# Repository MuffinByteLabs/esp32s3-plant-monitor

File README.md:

# ESP32-S3 Plant Monitor — Rev A

**Ray Malik** · [muffinbytelabs.com](https://muffinbytelabs.com) · [muffinbytelabs@gmail.com](mailto:muffinbytelabs@gmail.com)

A solo hardware project taken the whole way: requirements → schematic capture → 4-layer layout → DFM → fab and assembly order → bring-up. Every schematic, review, waiver and decision in this repo is my own work.

Wi-Fi plant monitor: soil moisture, temperature / humidity / pressure, and ambient light, USB-C powered with 1-cell LiPo charging and automatic USB↔battery hand-over. Native-USB programming, no bridge chip. KiCad 10 hierarchical schematic, **4-layer board** (signal / GND / GND / signal, JLC04161H-7628), 62.5 × 44.5 mm, ordered fabricated and assembled at JLCPCB on **2026-08-21**.

| | |
|---|---|
| **MCU** | ESP32-S3-WROOM-1-N8, native USB — no bridge chip |
| **Sensors** | BME280 (temperature / humidity / pressure) · VEML7700 (ambient light) · DFRobot SEN0193 capacitive soil probe |
| **Power** | USB-C 5 V → PPTC + TVS → AP2112K-3.3 (600 mA) · MCP73831 1S LiPo charger · discrete USB↔battery load share, hand-over in ≈50–100 ms |
| **Sleep** | ≈210 µA as built (≈90 µA with the power LED unfitted) ⇒ ~100 days on a 500 mAh cell |
| **Board** | 62.5 × 44.5 mm · 4-layer, JLC04161H-7628 · 1.6 mm · lead-free HASL · 404 track segments, 154 vias |
| **Verification** | 6 written reviews · 20 packages / 69 placements checked against datasheets |
| **Built** | 5 boards fabricated + assembled for ≈$49 after coupons, every part pre-stocked in the JLC library |
| **Tools** | KiCad 10 · JLCPCB Standard PCBA |

## Start here

Everything below opens in the browser — no KiCad install, no downloads.

| | |
|---|---|
| 📐 **[Schematic (PDF, 8 sheets)](docs/ESP32S3_PlantMonitor_RevA_Schematic.pdf)** | The whole design, plotted from the board file that was ordered |
| 📄 **[Design document](docs/ESP32S3_Plant_Monitor_Final_Design_Document.md)** | Every component and why it is there, written to be read by someone who is not a PCB engineer |
| 🔍 **[Design reviews — 6 on file](docs/reviews/)** | Real review records with findings, severities and fixes. The pre-fab review caught **3 blocking errors** — floating USB-C ground pins, a missing battery-sense chain, and a stale BOM — all resolved before ordering |
| 🧭 **[What I'd change in Rev B](docs/RevB_Upgrade_Plan.md)** | Ranked upgrades with a three-way charger-IC comparison and a costed path from 210 µA to 15–35 µA |
| 🧪 **[Engineering notes](docs/Engineering_Notes.md)** | Bench measurements: soil calibration, the three-layer battery-protection analysis, the hand-over walkthrough |
| 🏭 **[Frozen manufacturing package](fabrication/revA/)** | The exact gerber zip, BOM and CPL uploaded to JLCPCB, beside [`ORDER_NOTES.md`](fabrication/revA/ORDER_NOTES.md) — every setting the board was ordered with |
| 🔧 **[Bring-up guide](docs/BringUp_Guide.md)** | First-power procedure, expected voltages, probe points, troubleshooting |
| 🖨 **[Fab layer plots (PDF)](docs/ESP32S3_PlantMonitor_RevA_FabLayers.pdf)** | All four copper layers, both silks, mask and paste — what the fab actually receives |

| Top | Bottom |
|---|---|
|  |  |

## What this board demonstrates

- **4-layer discipline** — dual unbroken ground planes, zero signals on the inner layers, a via at every decoupler, stitching around the antenna keep-out.
- **RF module integration** — antenna nose overhanging the board edge, all-layer keepout, ground ring, and a panel-rail instruction written into the fab remark so breakaway tabs cannot sit under the overhang.
- **USB 2.0 pair** at ≈90 Ω coupled geometry, length-matched, no vias, ESD in copper order.
- **Power-path design with numbers** — fuse → TVS → LDO, an automatic USB↔battery hand-over sized so the switch completes in ≈50–100 ms, and a 210 µA sleep budget with a named dominant contributor.
- **Manufacturing fluency** — DFM checked against JLCPCB's live capability pages, part-tier economics understood before ordering, pre-stocked parts library, DDP tariff handling.
- **A documentation trail** — two design reviews, a placement review, a finishing review, a final layout audit, and order notes, all on record here.

## What I'd change in Rev B

- **The power path is discrete, and it shows.** MCP73831 + Schottky + P-FET load-sharing works, but it has a ≈50–100 ms body-diode notch at USB unplug, a Vgs-dependent switch point, and no charge safety timer. Rev B replaces the four-part cluster with one IC — [BQ24075 vs MCP73871 vs TPS2113A, compared](docs/RevB_Upgrade_Plan.md#1-integrated-power-path-the-headline-upgrade).
- **210 µA of sleep current is too high**, and the power LED alone is 120 µA of it. LED on a solder jumper, a nanopower LDO, and a switched sense divider get it to 15–35 µA — months to years of standby instead of weeks.
- **No series element on the soil-probe ADC input.** The probe cable is a metre-long antenna into a bare pin; Rev A has only a parallel pull-down. Series resistor plus TVS at J2 next time.
- **Four layers were bought for margin, not for speed.** The fastest signal on this board is USB Full Speed — a disciplined 2-layer board would have worked. The reasoning for spending the extra layers is written down in [`docs/KiCad_Settings_RevA.md`](docs/KiCad_Settings_RevA.md).

<details>
<summary><strong>Repository map</strong> — 24 documents, KiCad sources, frozen fab package, datasheets</summary>

| Path | What |
|---|---|
| [`hardware/`](hardware/) | KiCad 10 project — root sheet + sheets 02–08, libraries in `hardware/libs/`. Library paths are `${KIPRJMOD}`-relative; keep `libs/` inside `hardware/`. |
| [`fabrication/revA/`](fabrication/revA/) | The frozen order package: gerber zip, BOM, CPL, and `ORDER_NOTES.md` (§7 = the as-ordered record) |
| **Documents** | |
| [`docs/ESP32S3_PlantMonitor_RevA_Schematic.pdf`](docs/ESP32S3_PlantMonitor_RevA_Schematic.pdf) | All 8 schematic sheets, plotted from the ordered board file |
| [`docs/ESP32S3_PlantMonitor_RevA_FabLayers.pdf`](docs/ESP32S3_PlantMonitor_RevA_FabLayers.pdf) | Layer-by-layer fab plots |
| [`docs/ESP32S3_Plant_Monitor_Final_Design_Document.md`](docs/ESP32S3_Plant_Monitor_Final_Design_Document.md) | The full design document — as-built designators throughout; Addendum A holds the renumbering record |
| [`docs/PROJECT_STATUS.md`](docs/PROJECT_STATUS.md) | Rev A order and build log: what was ordered, what it cost, order-day problems and fixes, waivers on record |
| [`docs/BringUp_Guide.md`](docs/BringUp_Guide.md) | First-power procedure, expected voltages, probe points |
| [`docs/PinMap_CheatSheet.md`](docs/PinMap_CheatSheet.md) | GPIO / net / connector map, as built |
| [`docs/Engineering_Notes.md`](docs/Engineering_Notes.md) | Bench notes: calibration values, battery-protection analysis, hand-over walkthrough |
| [`docs/ESP32S3_PlantMonitor_RevA_BOM.md`](docs/ESP32S3_PlantMonitor_RevA_BOM.md) | BOM as a readable table (the [`.xlsx`](docs/ESP32S3_PlantMonitor_RevA_BOM.xlsx) is the editable source) |
| **Layout rulebooks** | |
| [`docs/Hard_Rules_Layout_RevA.md`](docs/Hard_Rules_Layout_RevA.md) | The graded rulebook — LAW vs STRONG PRACTICE, plus 4-layer amendments |
| [`docs/Routing_Guide_RevA_4Layer.md`](docs/Routing_Guide_RevA_4Layer.md) | Layer strategy, net-by-net routing order, via craft |
| [`docs/KiCad_Settings_RevA.md`](docs/KiCad_Settings_RevA.md) | Every board-setup value and the reasoning behind it |
| [`docs/Layout_Readiness_and_Placement_Guide_RevA.md`](docs/Layout_Readiness_and_Placement_Guide_RevA.md) | Footprint verification + placement playbook |
| [`docs/Footprint_Check_ESP32S3_PlantMonitor_RevA.md`](docs/Footprint_Check_ESP32S3_PlantMonitor_RevA.md) | All 20 packages / 69 placements, each checked against its datasheet |
| [`docs/Footprint_Terms_and_Leeway_Guide.md`](docs/Footprint_Terms_and_Leeway_Guide.md) | Plain-English footprint terms and how much tolerance actually matters |
| [`docs/Fabrication_File_Primer.md`](docs/Fabrication_File_Primer.md) | What each gerber and drill file is, and why |
| [`docs/Finishing_Guide_RevA.md`](docs/Finishing_Guide_RevA.md) | Silkscreen, branding and pre-order finishing pass |
| [`docs/RevB_Upgrade_Plan.md`](docs/RevB_Upgrade_Plan.md) | Ranked upgrades, integrated power path first |
| **Reviews** | |
| [`docs/reviews/`](docs/reviews/README.md) | All six reviews, [indexed here](docs/reviews/README.md) with date, scope, method and outcome |
| **References** | |
| [`references/datasheets/`](references/datasheets/) | Vendor datasheets for every part — [indexed here](references/datasheets/README.md) |
| [`references/JLCPCB_Capabilities_2026-08.md`](references/JLCPCB_Capabilities_2026-08.md) | Capability quick-sheet used for DFM |
| [`references/reference-designs/`](references/reference-designs/) | Espressif DevKitC-1 schematic |
| [`firmware/`](firmware/) | The hardware→firmware contract: thresholds, sequences and pin duties the board imposes |

</details>

## What's next

Boards arrive early September. Bring-up follows [`docs/BringUp_Guide.md`](docs/BringUp_Guide.md) — measured results go into its record sheet, and a photograph of the working board replaces the render above.

Questions, or hiring: **[muffinbytelabs@gmail.com](mailto:muffinbytelabs@gmail.com)** · [muffinbytelabs.com](https://muffinbytelabs.com)

## License

Hardware design files and documentation are released under the **CERN Open Hardware Licence v2 — Permissive** (see [`LICENSE`](LICENSE)). Vendor datasheets in `references/datasheets/` remain the property of their respective manufacturers and are included for convenience only.

## Safety notes for anyone building this board

1. **Meter the battery plug polarity** before it ever touches J3 — the charge LED is not proof of polarity.
2. **Protected cells only**, and never store the board with a battery attached (≈210 µA sleep floor).
3. **Firmware enforces the battery limits**: no Wi-Fi TX below ~3.5 V, deep sleep at 3.0 V.

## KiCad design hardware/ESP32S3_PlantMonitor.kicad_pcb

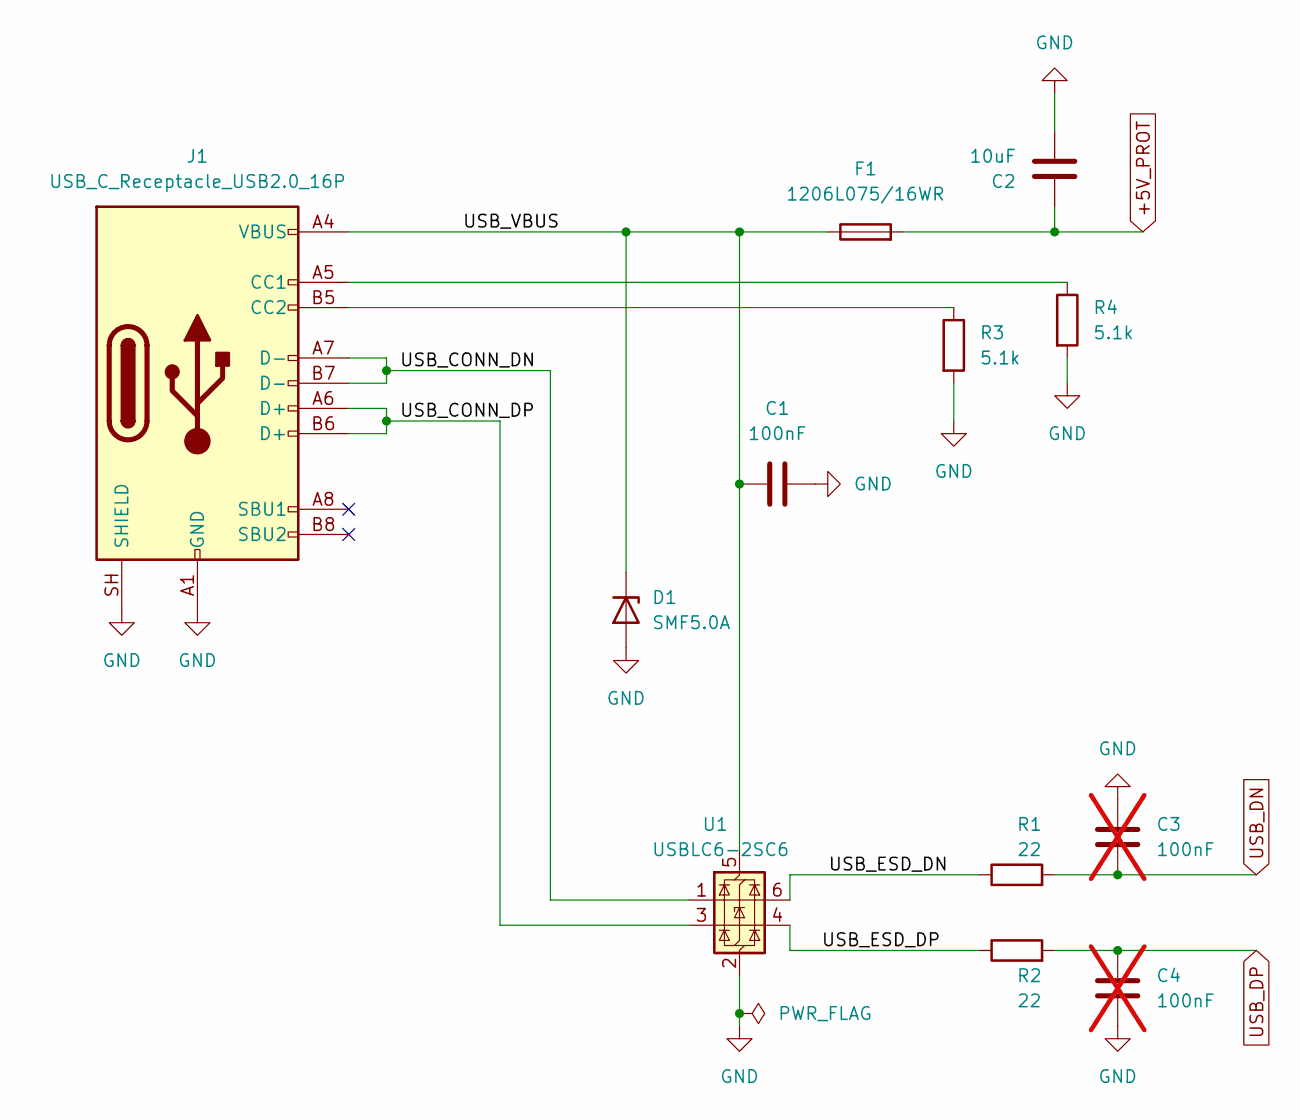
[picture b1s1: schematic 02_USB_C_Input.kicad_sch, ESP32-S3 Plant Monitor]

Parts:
C1: 100nF; C_0603_1608Metric; LCSC Part C14663
C2: 10uF; C_0805_2012Metric; LCSC Part C15850
C3, C4: 100nF; C_0603_1608Metric; LCSC Part C14663; not fitted
D1: SMF5.0A; D_SOD-123F; LCSC Part C2980403
F1: 1206L075/16WR; Fuse_1206_3216Metric; LCSC Part C371166
J1: USB_C_Receptacle_USB2.0_16P; USB_C_Receptacle_HRO_TYPE-C-31-M-12; LCSC Part C165948
R1, R2: 22; R_0603_1608Metric; LCSC Part C23345
R3, R4: 5.1k; R_0603_1608Metric; LCSC Part C23186
U1: USBLC6-2SC6; SOT-23-6; LCSC Part C7519

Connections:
+5V_PROT: C2.1, F1.2; also elsewhere on the board
/02_USB_C_Input/USB_CONN_DN: J1.A7 (D-), J1.B7 (D-), U1.1 (I/O1)
/02_USB_C_Input/USB_CONN_DP: J1.A6 (D+), J1.B6 (D+), U1.3 (I/O2)
/02_USB_C_Input/USB_ESD_DN: R1.1, U1.6 (I/O1)
/02_USB_C_Input/USB_ESD_DP: R2.1, U1.4 (I/O2)
/02_USB_C_Input/USB_VBUS: C1.1, D1.1 (K), F1.1, J1.A4 (VBUS), J1.A9 (VBUS), J1.B4 (VBUS), J1.B9 (VBUS), U1.5 (VBUS)
GND: C1.2, C2.2, C3.2, C4.1, D1.2 (A), J1.A1 (GND), J1.A12 (GND), J1.B1 (GND), J1.B12 (GND), J1.SH (SHIELD), R3.2, R4.2, U1.2 (GND); also elsewhere on the board
unnamed: J1.A5 (CC1), R4.1
unnamed: J1.B5 (CC2), R3.1
USB_DN: C3.1, R1.2; also elsewhere on the board
USB_DP: C4.2, R2.2; also elsewhere on the board

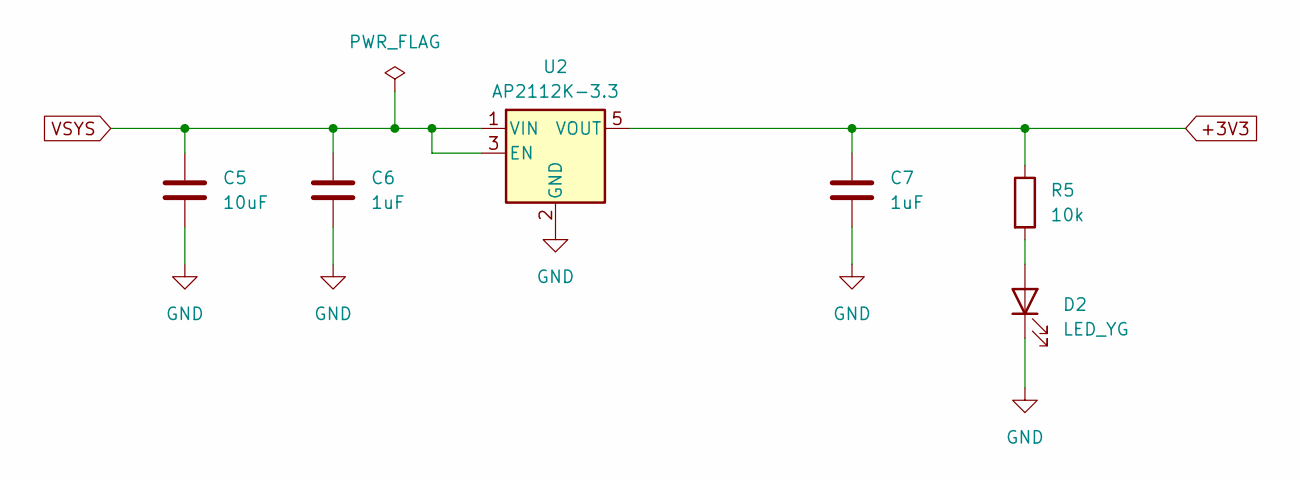
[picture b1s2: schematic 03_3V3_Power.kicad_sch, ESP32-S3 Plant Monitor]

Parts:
C5: 10uF; C_0805_2012Metric; LCSC Part C15850
C6, C7: 1uF; C_0603_1608Metric; LCSC Part C15849
D2: LED_YG; LED_0603_1608Metric; LCSC Part C2289
R5: 10k; R_0603_1608Metric; LCSC Part C25804
U2: AP2112K-3.3; SOT-23-5; LCSC Part C51118

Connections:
+3V3: C7.1, R5.1, U2.5 (VOUT); also elsewhere on the board
GND: C5.2, C6.2, C7.2, D2.1 (K), U2.2 (GND); also elsewhere on the board
unnamed: D2.2 (A), R5.2
VSYS: C5.1, C6.1, U2.1 (VIN), U2.3 (EN); also elsewhere on the board

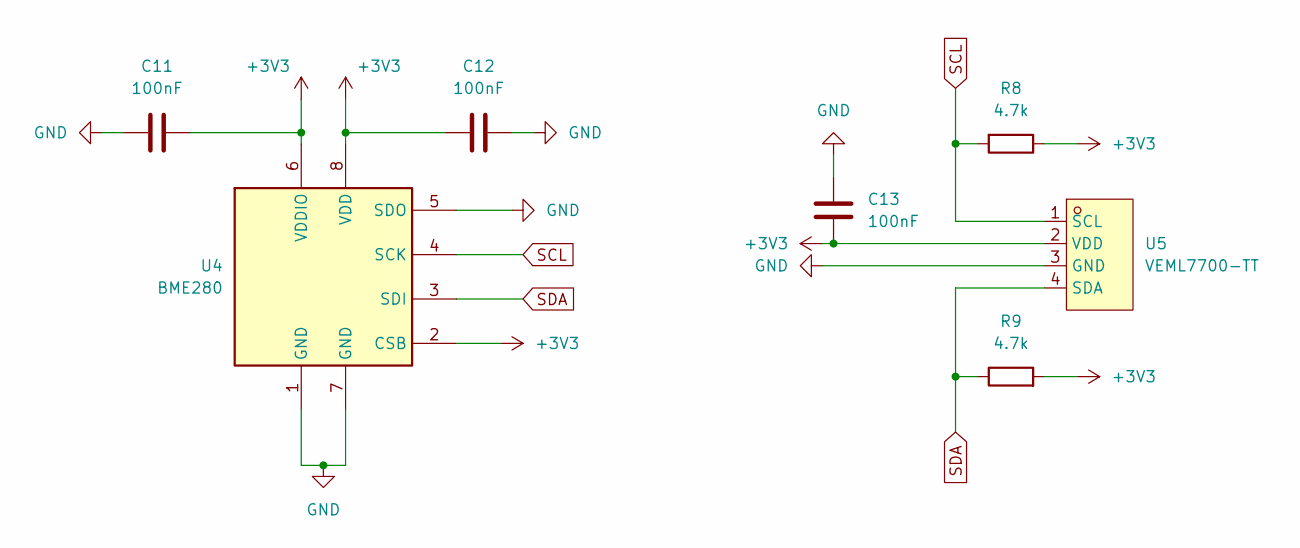
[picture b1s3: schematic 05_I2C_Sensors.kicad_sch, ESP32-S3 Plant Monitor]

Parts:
C11, C12, C13: 100nF; C_0603_1608Metric; LCSC Part C14663
R8, R9: 4.7k; R_0603_1608Metric; LCSC Part C23162
U4: BME280; Bosch_LGA-8_2.5x2.5mm_P0.65mm_ClockwisePinNumbering; LCSC Part C92489
U5: VEML7700-TT; SENSOR-SMD_EML7700-TT; MPN VEML7700-TT; LCSC Part C1850416

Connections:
+3V3: C11.2, C12.2, C13.2, R8.1, R9.2, U4.2 (CSB), U4.6 (VDDIO), U4.8 (VDD), U5.2 (VDD); also elsewhere on the board
GND: C11.1, C12.1, C13.1, U4.1 (GND), U4.5 (SDO), U4.7 (GND), U5.3 (GND); also elsewhere on the board
SCL: R8.2, U4.4 (SCK), U5.1 (SCL); also elsewhere on the board
SDA: R9.1, U4.3 (SDI), U5.4 (SDA); also elsewhere on the board

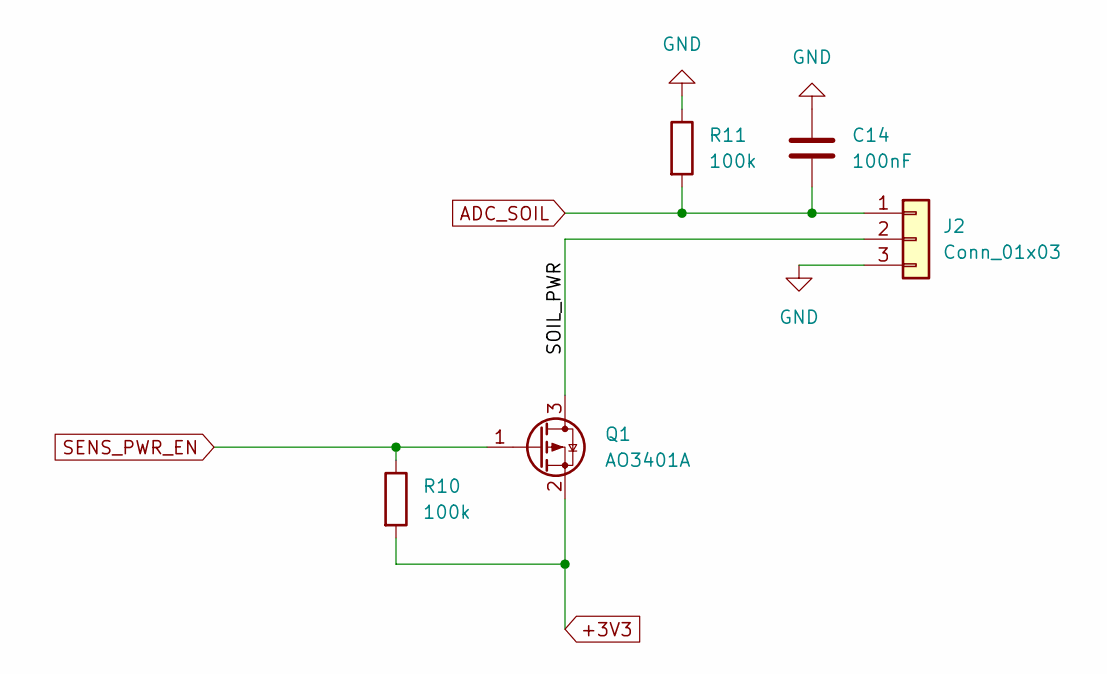
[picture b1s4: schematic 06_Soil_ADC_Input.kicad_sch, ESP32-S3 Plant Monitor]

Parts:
C14: 100nF; C_0603_1608Metric; LCSC Part C14663
J2: Conn_01x03; JST_PH_S3B-PH-K_1x03_P2.00mm_Horizontal; LCSC Part C157929
Q1: AO3401A; SOT-23; LCSC Part C15127
R10, R11: 100k; R_0603_1608Metric; LCSC Part C25803

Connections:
+3V3: Q1.2 (S), R10.2; also elsewhere on the board
/06_Soil_Probe_Input/SOIL_PWR: J2.2, Q1.3 (D)
ADC_SOIL: C14.2, J2.1, R11.2; also elsewhere on the board
GND: C14.1, J2.3, R11.1; also elsewhere on the board
SENS_PWR_EN: Q1.1 (G), R10.1; also elsewhere on the board

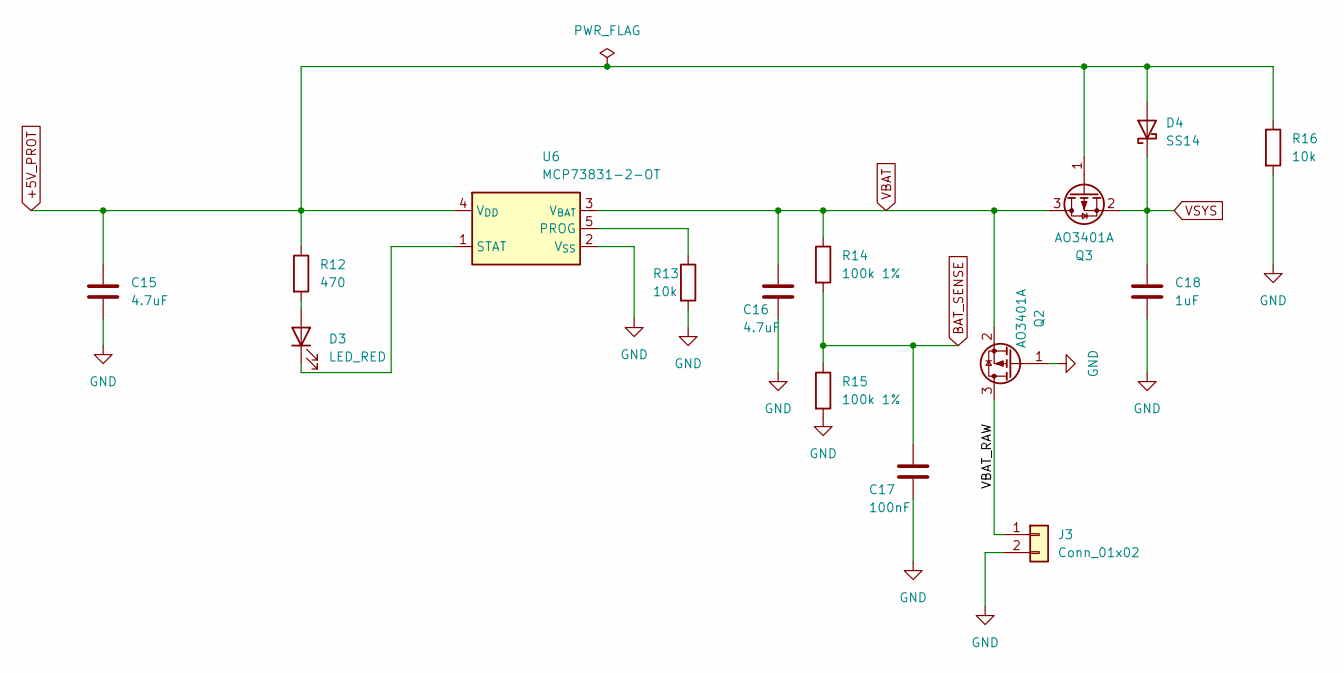
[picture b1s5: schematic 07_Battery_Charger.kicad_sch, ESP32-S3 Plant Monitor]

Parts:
C15, C16: 4.7uF; C_0603_1608Metric; LCSC Part C19666
C17: 100nF; C_0603_1608Metric; LCSC Part C14663
C18: 1uF; C_0603_1608Metric; LCSC Part C15849
D3: LED_RED; LED_0603_1608Metric; LCSC Part C2286
D4: SS14; D_SMA; LCSC Part C2480
J3: Conn_01x02; JST_PH_S2B-PH-K_1x02_P2.00mm_Horizontal; LCSC Part C173752
Q2, Q3: AO3401A; SOT-23; LCSC Part C15127
R12: 470; R_0603_1608Metric; LCSC Part C23179
R13, R16: 10k; R_0603_1608Metric; LCSC Part C25804
R14, R15: 100k 1%; R_0603_1608Metric; LCSC Part C25803
U6: MCP73831-2-OT; SOT-23-5; LCSC Part C424093

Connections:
+5V_PROT: C15.1, D4.2 (A), Q3.1 (G), R12.1, R16.1, U6.4 (V_{DD}); also elsewhere on the board
/07_Battery_PowerPath/VBAT_RAW: J3.1, Q2.3 (D)
BAT_SENSE: C17.1, R14.2, R15.1; also elsewhere on the board
GND: C15.2, C16.2, C17.2, C18.2, J3.2, Q2.1 (G), R13.2, R15.2, R16.2, U6.2 (V_{SS}); also elsewhere on the board
unnamed: D3.2 (A), R12.2
unnamed: D3.1 (K), U6.1 (STAT)
unnamed: R13.1, U6.5 (PROG)
VBAT: C16.1, Q2.2 (S), Q3.3 (D), R14.1, U6.3 (V_{BAT}); also elsewhere on the board
VSYS: C18.1, D4.1 (K), Q3.2 (S); also elsewhere on the board

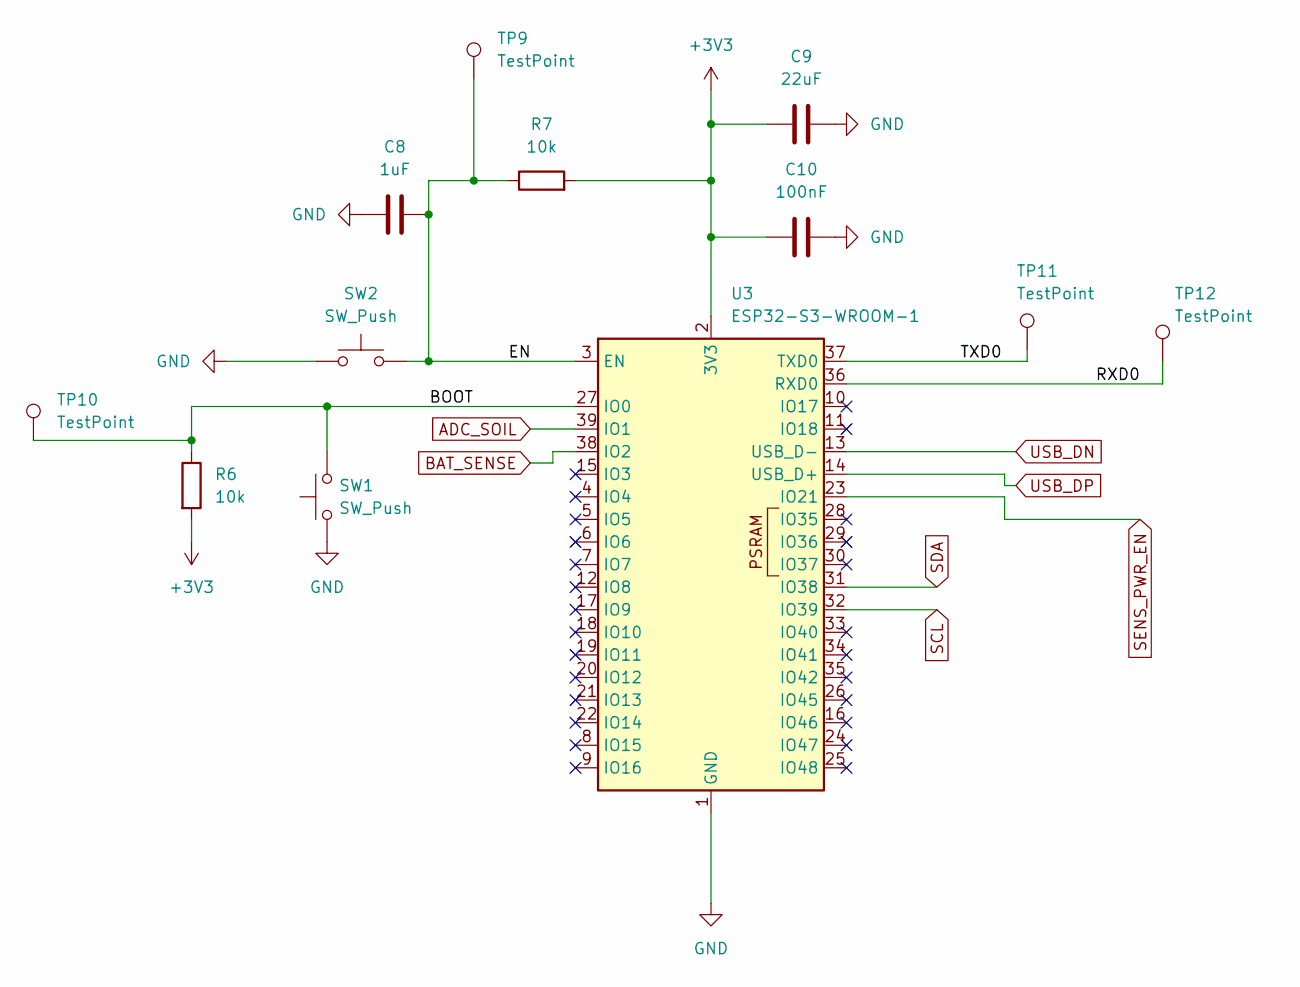
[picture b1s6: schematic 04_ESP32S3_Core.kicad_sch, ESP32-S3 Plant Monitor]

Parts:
C8: 1uF; C_0603_1608Metric; LCSC Part C15849
C9: 22uF; C_0805_2012Metric; LCSC Part C45783
C10: 100nF; C_0603_1608Metric; LCSC Part C14663
R6, R7: 10k; R_0603_1608Metric; LCSC Part C25804
SW1, SW2: SW_Push; SW-SMD_4P-L5.1-W5.1-P3.70-LS6.5-TL_H1.5; LCSC Part C318884
TP9, TP10: TestPoint; TestPoint_Pad_D1.5mm
TP11, TP12: TestPoint; TestPoint_THTPad_D2.0mm_Drill1.0mm
U3: ESP32-S3-WROOM-1; LCSC Part C2913198

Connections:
+3V3: C9.1, C10.1, R6.2, R7.2, U3.2 (3V3); also elsewhere on the board
/04_ESP32S3_Core/BOOT: R6.1, SW1.2, TP10.1 (1_1), U3.27 (IO0)
/04_ESP32S3_Core/EN: C8.2, R7.1, SW2.2, TP9.1 (1_1), U3.3 (EN)
/04_ESP32S3_Core/RXD0: TP12.1 (1_1), U3.36 (RXD0)
/04_ESP32S3_Core/TXD0: TP11.1 (1_1), U3.37 (TXD0)
ADC_SOIL: U3.39 (IO1); also elsewhere on the board
BAT_SENSE: U3.38 (IO2); also elsewhere on the board
GND: C8.1, C9.2, C10.2, SW1.1, SW2.1, U3.1 (GND), U3.40 (GND), U3.41 (GND); also elsewhere on the board
SCL: U3.32 (IO39); also elsewhere on the board
SDA: U3.31 (IO38); also elsewhere on the board
SENS_PWR_EN: U3.23 (IO21); also elsewhere on the board
USB_DN: U3.13 (USB_D-); also elsewhere on the board
USB_DP: U3.14 (USB_D+); also elsewhere on the board

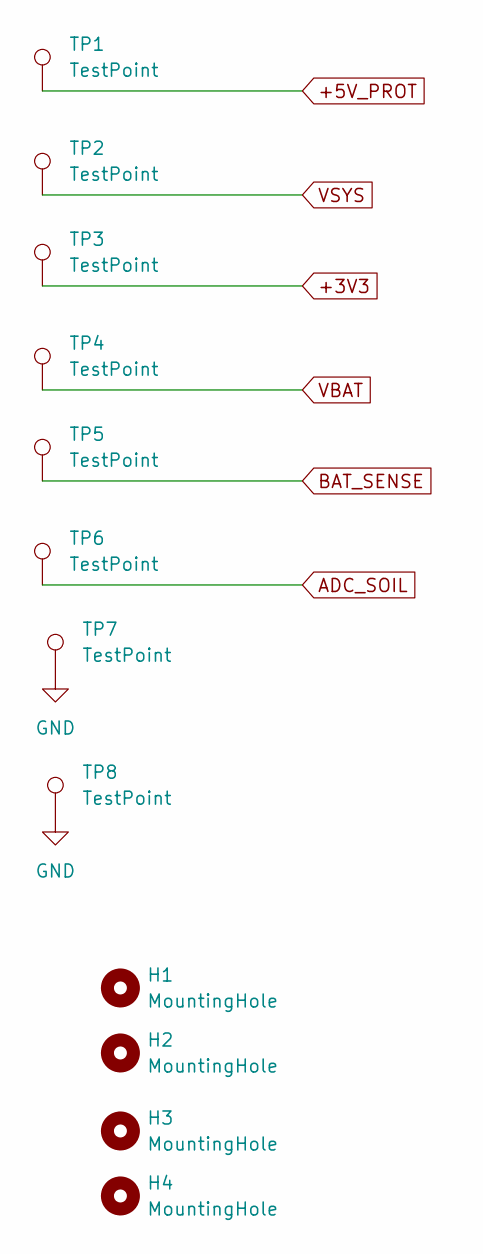
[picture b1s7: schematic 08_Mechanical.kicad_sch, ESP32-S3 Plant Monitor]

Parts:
H1, H2, H3, H4: MountingHole; MountingHole_3.2mm_M3
TP1, TP2, TP3, TP4, TP5, TP6, TP7: TestPoint; TestPoint_Pad_D1.5mm
TP8: TestPoint; TestPoint_THTPad_D2.0mm_Drill1.0mm

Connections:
+3V3: TP3.1 (1_1); also elsewhere on the board
+5V_PROT: TP1.1 (1_1); also elsewhere on the board
ADC_SOIL: TP6.1 (1_1); also elsewhere on the board
BAT_SENSE: TP5.1 (1_1); also elsewhere on the board
GND: TP7.1 (1_1), TP8.1 (1_1); also elsewhere on the board
VBAT: TP4.1 (1_1); also elsewhere on the board
VSYS: TP2.1 (1_1); also elsewhere on the board

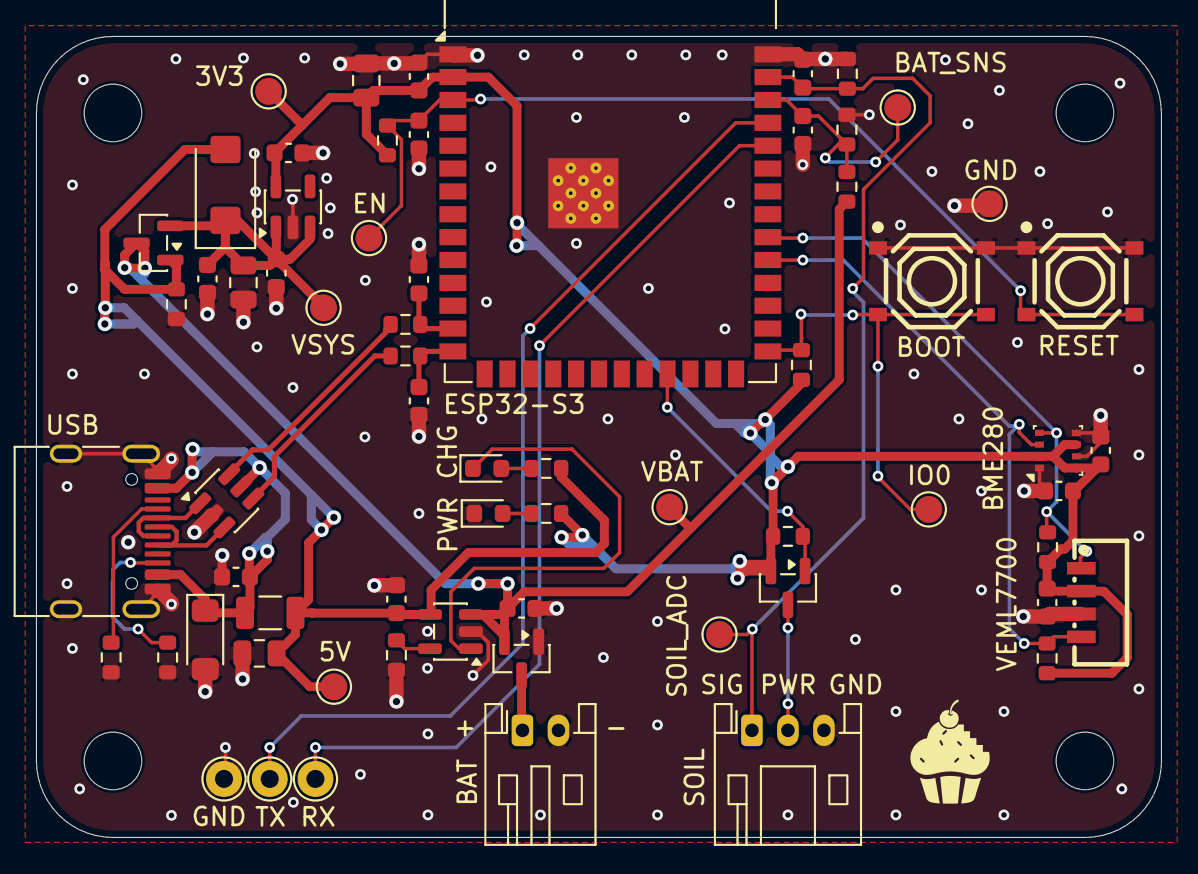
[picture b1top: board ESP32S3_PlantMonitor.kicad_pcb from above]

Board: 4 copper layers, 62.5 x 44.5 mm, 70 parts (0 on the bottom side), 29 nets.

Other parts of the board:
G1: muffinByteLogo_2x

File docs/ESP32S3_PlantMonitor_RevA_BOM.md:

# ESP32-S3 Plant Monitor — Rev A Bill of Materials

*GENERATED FROM THE SCHEMATIC 2026-07-20 (53 parts / 29 lines; LCSC fields verified in-file). The schematic is the master — regenerate this sheet after any change. Library status (Basic/Extended) and stock are LIVE values: re-verify every line on jlcpcb.com/parts at order time. Test points & mounting holes intentionally excluded (bare copper / holes).*

> The spreadsheet this table is generated from lives beside it as [`ESP32S3_PlantMonitor_RevA_BOM.xlsx`](ESP32S3_PlantMonitor_RevA_BOM.xlsx). For what was **actually ordered** on 2026-08-21 — including the two substitutions made on order day — see [`fabrication/revA/BOM-ESP32S3_PlantMonitor.csv`](../fabrication/revA/BOM-ESP32S3_PlantMonitor.csv).

| # | Category | Designators | Qty | Value | MPN | LCSC # | Footprint (package) | Library | Populate | Notes |
|---|---|---|---|---|---|---|---|---|---|---|
| 1 | 1 ICs & module | U1 | 1 | USBLC6-2SC6 | USBLC6-2SC6 | C7519 | SOT-23-6 | Extended | Yes |  |
| 2 | 1 ICs & module | U2 | 1 | AP2112K-3.3 | AP2112K-3.3TRG1 | C51118 | SOT-23-5 | Extended | Yes | 3.3 V / 600 mA |
| 3 | 1 ICs & module | U3 | 1 | ESP32-S3-WROOM-1 | ESP32-S3-WROOM-1-N8 | C2913198 | ESP32-S3-WROOM-1 | Extended | Yes | Standard PCBA tier only (module size) |
| 4 | 1 ICs & module | U4 | 1 | BME280 | BME280 | C92489 | Bosch_LGA-8_2.5x2.5mm_P0.65mm_ClockwisePinNumbering | Extended | Yes | 0x76; keep vent clear, away from heat |
| 5 | 1 ICs & module | U5 | 1 | VEML7700-TT | VEML7700-TT | C1850416 | SENSOR-SMD_EML7700-TT | Extended | Yes | -TT = top-view window; 0x10 |
| 6 | 1 ICs & module | U6 | 1 | MCP73831-2-OT | MCP73831T-2ACI/OT | C424093 | SOT-23-5 | Extended | Yes | 4.20 V variant; PROG 10k -> ~100 mA |
| 7 | 2 Transistors | Q1, Q2, Q3 | 3 | AO3401A | AO3401A | C15127 | SOT-23 | Basic | Yes | Q1 soil switch / Q2 reverse guard / Q3 source select |
| 8 | 3 Diodes & LEDs | D1 | 1 | SMF5.0A | SMF5.0A | C2980403 | D_SOD-123F | Extended | Yes | TVS on USB_VBUS |
| 9 | 3 Diodes & LEDs | D2 | 1 | LED_YG | KT-0603YG | C2289 | LED_0603_1608Metric | Extended | Yes | Yellow-green Vf 2.0-2.2 V (correct chemistry for 3.3 V rail). 30-42 mcd -> dim at 120 uA by design; bench-check. Went Extended 2026-07. |
| 10 | 3 Diodes & LEDs | D3 | 1 | LED_RED | KT-0603R | C2286 | LED_0603_1608Metric | Basic | Yes | Red, ~6 mA from STAT |
| 11 | 3 Diodes & LEDs | D4 | 1 | SS14 | SS14 | C2480 | D_SMA | Basic | Yes | Power-path Schottky |
| 12 | 4 Connectors & electromech | F1 | 1 | 1206L075/16WR | 1206L075/16WR | C371166 | Fuse_1206_3216Metric | Verify | Yes | 0.75 A hold / 1.5 A trip / 16 V |
| 13 | 4 Connectors & electromech | J1 | 1 | USB_C_Receptacle_USB2.0_16P | TYPE-C-31-M-12 | C165948 | USB_C_Receptacle_HRO_TYPE-C-31-M-12 | Extended | Yes | KiCad ships exact footprint. Small handling fee. |
| 14 | 4 Connectors & electromech | J2 | 1 | Conn_01x03 | S3B-PH-K-S(LF)(SN) | C157929 | JST_PH_S3B-PH-K_1x03_P2.00mm_Horizontal | Verify | Yes | Soil: pin1 sig / pin2 pwr / pin3 GND. Buzz out cable. |
| 15 | 4 Connectors & electromech | J3 | 1 | Conn_01x02 | S2B-PH-K-S(LF)(SN) | C173752 | JST_PH_S2B-PH-K_1x02_P2.00mm_Horizontal | Verify | Yes | Battery: pin1 = +. METER PLUG POLARITY FIRST. |
| 16 | 4 Connectors & electromech | SW1, SW2 | 2 | SW_Push | TS-1187A-B-A-B | C318884 | SW-SMD_4P-L5.1-W5.1-P3.70-LS6.5-TL_H1.5 | Basic | Yes | Project footprint, pads renumbered 1/1/2/2 (verified vs datasheet A-B/C-D pairing) |
| 17 | 5 Resistors 0603 | R1, R2 | 2 | 22 | 0603WAF220JT5E | C23345 | R_0603_1608Metric | Basic | Yes | USB series |
| 18 | 5 Resistors 0603 | R10, R11 | 2 | 100k | 0603WAF1003T5E | C25803 | R_0603_1608Metric | Basic | Yes | All +-1% |
| 19 | 5 Resistors 0603 | R12 | 1 | 470 | 0603WAF4700T5E | C23179 | R_0603_1608Metric | Basic | Yes | Charge-LED limit ~6 mA |
| 20 | 5 Resistors 0603 | R13, R16, R5, R6, R7 | 5 | 10k | RC0603FR-0710KL | C98220 | R_0603_1608Metric | Extended | Yes | Stock was 0 on 2026-07-20 - re-check; alternate: YAGEO RC0603FR-0710KL = C98220 (Extended) — was C25804 (Uni-Royal, Basic) — JLC pre-order failed 2026-08-18, switched to Yageo C98220 |
| 21 | 5 Resistors 0603 | R14, R15 | 2 | 100k 1% | 0603WAF1003T5E | C25803 | R_0603_1608Metric | Basic | Yes | All +-1% |
| 22 | 5 Resistors 0603 | R3, R4 | 2 | 5.1k | 0603WAF5101T5E | C23186 | R_0603_1608Metric | Basic | Yes | CC pull-downs, one per pin |
| 23 | 5 Resistors 0603 | R8, R9 | 2 | 4.7k | 0603WAF4701T5E | C23162 | R_0603_1608Metric | Basic | Yes | I2C pull-ups |
| 24 | 6 Capacitors | C1, C10, C11, C12, C13, C14, C17 | 7 | 100nF | CC0603KRX7R9BB104 | C14663 | C_0603_1608Metric | Basic | Yes |  |
| 25 | 6 Capacitors | C15, C16 | 2 | 4.7uF | CL10A475KO8NNNC | C19666 | C_0603_1608Metric | Basic | Yes | 16 V X5R — charger in/out |
| 26 | 6 Capacitors | C18, C6, C7, C8 | 4 | 1uF | CL10A105KB8NNNC | C15849 | C_0603_1608Metric | Basic | Yes | 50 V X5R |
| 27 | 6 Capacitors | C2, C5 | 2 | 10uF | CL21A106KAYNNNE | C15850 | C_0805_2012Metric | Basic | Yes | 25 V X5R — 5 V-rail & VSYS bulk (alt: Murata C440198) |
| 28 | 6 Capacitors | C3, C4 | 2 | 100nF | CC0603KRX7R9BB104 | C14663 | C_0603_1608Metric | Basic | No (DNP) | DNP - footprint only, not assembled. |
| 29 | 6 Capacitors | C9 | 1 | 22uF | CL21A226MAQNNNE | C45783 | C_0805_2012Metric | Basic | Yes | 25 V X5R — module bulk |

## Not assembled by JLCPCB — to buy and attach myself

| Item | Spec | Plugs into | Where | Notes |
|---|---|---|---|---|
| DFRobot SEN0193 soil probe | 3.3-5.5 V, out 0-3.0 V (~2.2 V max @3.3 V), ~5 mA | J2 | DigiKey/DFRobot/Amazon | Buzz out cable order first. Calibration (direct chain): wet ~1465 / dry ~2900 raw. |
| 1S protected LiPo | 3.7 V, JST-PH; bench cell: PKCell LP503035 500 mAh | J3 | Battery retailer | PCM required. METER PLUG POLARITY BEFORE FIRST CONNECT - charge LED does NOT prove polarity. Never store with battery attached. |
| PH-to-PH 3-pin cable (if needed) | JST PH 2.0 | J2 | ~$1 generic | Only if probe cable ends DuPont-style. |

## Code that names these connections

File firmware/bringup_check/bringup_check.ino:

// bringup_check.ino — Rev A hardware bring-up helper
//
// Covers BringUp_Guide.md steps 4, 5 and 6 in one flash, and pre-loads the
// numbers step C-8 needs. Deliberately DOES NOT sleep: the USB port on this
// board is the ESP32-S3's own USB Serial/JTAG peripheral, not a bridge chip,
// so a board in deep sleep has no COM port and every upload after that needs
// the hold-BOOT / tap-RESET dance. This sketch stays awake and keeps the port.
//
// There is no GPIO-controlled LED on Rev A — D2 is hardwired to +3V3 through
// R5 and D3 belongs to the charger — so "is it alive?" is answered over serial.
//
// Pins from docs/PinMap_CheatSheet.md (I2C re-pinned to IO38/IO39 2026-08-15).

#include <Wire.h>
#include "esp_system.h"

#define PIN_SDA          38
#define PIN_SCL          39
#define PIN_ADC_SOIL      1   // ADC1_CH0, direct, no divider
#define PIN_BAT_SENSE     2   // ADC1_CH1, VBAT / 2 via R14/R15
#define PIN_SENS_PWR_EN  21   // LOW = probe on. Left released here.
#define ADC_SAMPLES      16

static const char *resetReasonName(esp_reset_reason_t r) {
  switch (r) {
    case ESP_RST_POWERON:  return "POWERON  (cold start / battery connect)";
    case ESP_RST_EXT:      return "EXT      (RESET button, SW2)";
    case ESP_RST_SW:       return "SW       (software restart)";
    case ESP_RST_PANIC:    return "PANIC    (exception / crash)";
    case ESP_RST_INT_WDT:  return "INT_WDT  (interrupt watchdog)";
    case ESP_RST_TASK_WDT: return "TASK_WDT (task watchdog)";
    case ESP_RST_WDT:      return "WDT      (other watchdog)";
    case ESP_RST_DEEPSLEEP:return "DEEPSLEEP(woke from deep sleep)";
    case ESP_RST_BROWNOUT: return "BROWNOUT <-- THIS IS THE STEP 9 FAILURE";
    case ESP_RST_SDIO:     return "SDIO";
    default:               return "UNKNOWN";
  }
}

static uint32_t readAvgRaw(int pin) {
  uint32_t acc = 0;
  for (int i = 0; i < ADC_SAMPLES; i++) { acc += analogRead(pin); delay(2); }
  return acc / ADC_SAMPLES;
}

static uint32_t readAvgMv(int pin) {
  uint32_t acc = 0;
  for (int i = 0; i < ADC_SAMPLES; i++) { acc += analogReadMilliVolts(pin); delay(2); }
  return acc / ADC_SAMPLES;
}

void i2cScan() {
  Serial.println(F("  I2C scan on SDA=38 SCL=39:"));
  int found = 0;
  for (uint8_t addr = 1; addr < 127; addr++) {
    Wire.beginTransmission(addr);
    if (Wire.endTransmission() == 0) {
      found++;
      Serial.printf("    0x%02X  <-- %s\n", addr,
        addr == 0x76 ? "BME280   (expected)" :
        addr == 0x10 ? "VEML7700 (expected)" : "UNEXPECTED DEVICE");
    }
  }
  if (!found) Serial.println(F("    NOTHING FOUND. Check R8/R9 pull-ups, U4 SDO->GND, U5 solder."));
  else {
    Serial.printf("    %d device(s). Step 5 passes only with BOTH 0x76 and 0x10.\n", found);
  }
}

void setup() {
  // Probe stays off: released, so R10's pull-up holds Q1's gate high.
  pinMode(PIN_SENS_PWR_EN, INPUT);

  Serial.begin(115200);
  uint32_t t0 = millis();
  while (!Serial && (millis() - t0) < 3000) { delay(10); }
  delay(200);

  Serial.println();
  Serial.println(F("================================================"));
  Serial.println(F(" ESP32-S3 Plant Monitor Rev A - bring-up check"));
  Serial.println(F("================================================"));

  esp_reset_reason_t r = esp_reset_reason();
  Serial.printf("  Reset reason : %s\n", resetReasonName(r));
  Serial.printf("  Chip         : %s rev %d, %d core(s)\n",
                ESP.getChipModel(), ESP.getChipRevision(), ESP.getChipCores());
  Serial.printf("  Flash        : %u MB  (expect 8 for WROOM-1-N8)\n",
                (unsigned)(ESP.getFlashChipSize() / (1024 * 1024)));
  Serial.printf("  PSRAM        : %u bytes (expect 0 on N8)\n", (unsigned)ESP.getPsramSize());
  Serial.println();

  Wire.begin(PIN_SDA, PIN_SCL, 100000UL);
  i2cScan();
  Serial.println();

  analogReadResolution(12);
  analogSetPinAttenuation(PIN_ADC_SOIL,  ADC_11db);
  analogSetPinAttenuation(PIN_BAT_SENSE, ADC_11db);

  Serial.println(F("  Streaming ADC every 2 s. Ctrl-click reset (SW2) to re-run header."));
  Serial.println();
}

void loop() {
  uint32_t batRaw = readAvgRaw(PIN_BAT_SENSE);
  uint32_t batMv  = readAvgMv(PIN_BAT_SENSE);
  uint32_t soRaw  = readAvgRaw(PIN_ADC_SOIL);
  uint32_t soMv   = readAvgMv(PIN_ADC_SOIL);

  Serial.printf("BAT_SENSE %4u raw  %4u mV  -> VBAT ~%u mV   |   ADC_SOIL %4u raw  %4u mV\n",
                (unsigned)batRaw, (unsigned)batMv, (unsigned)(batMv * 2),
                (unsigned)soRaw, (unsigned)soMv);
  delay(2000);
}
